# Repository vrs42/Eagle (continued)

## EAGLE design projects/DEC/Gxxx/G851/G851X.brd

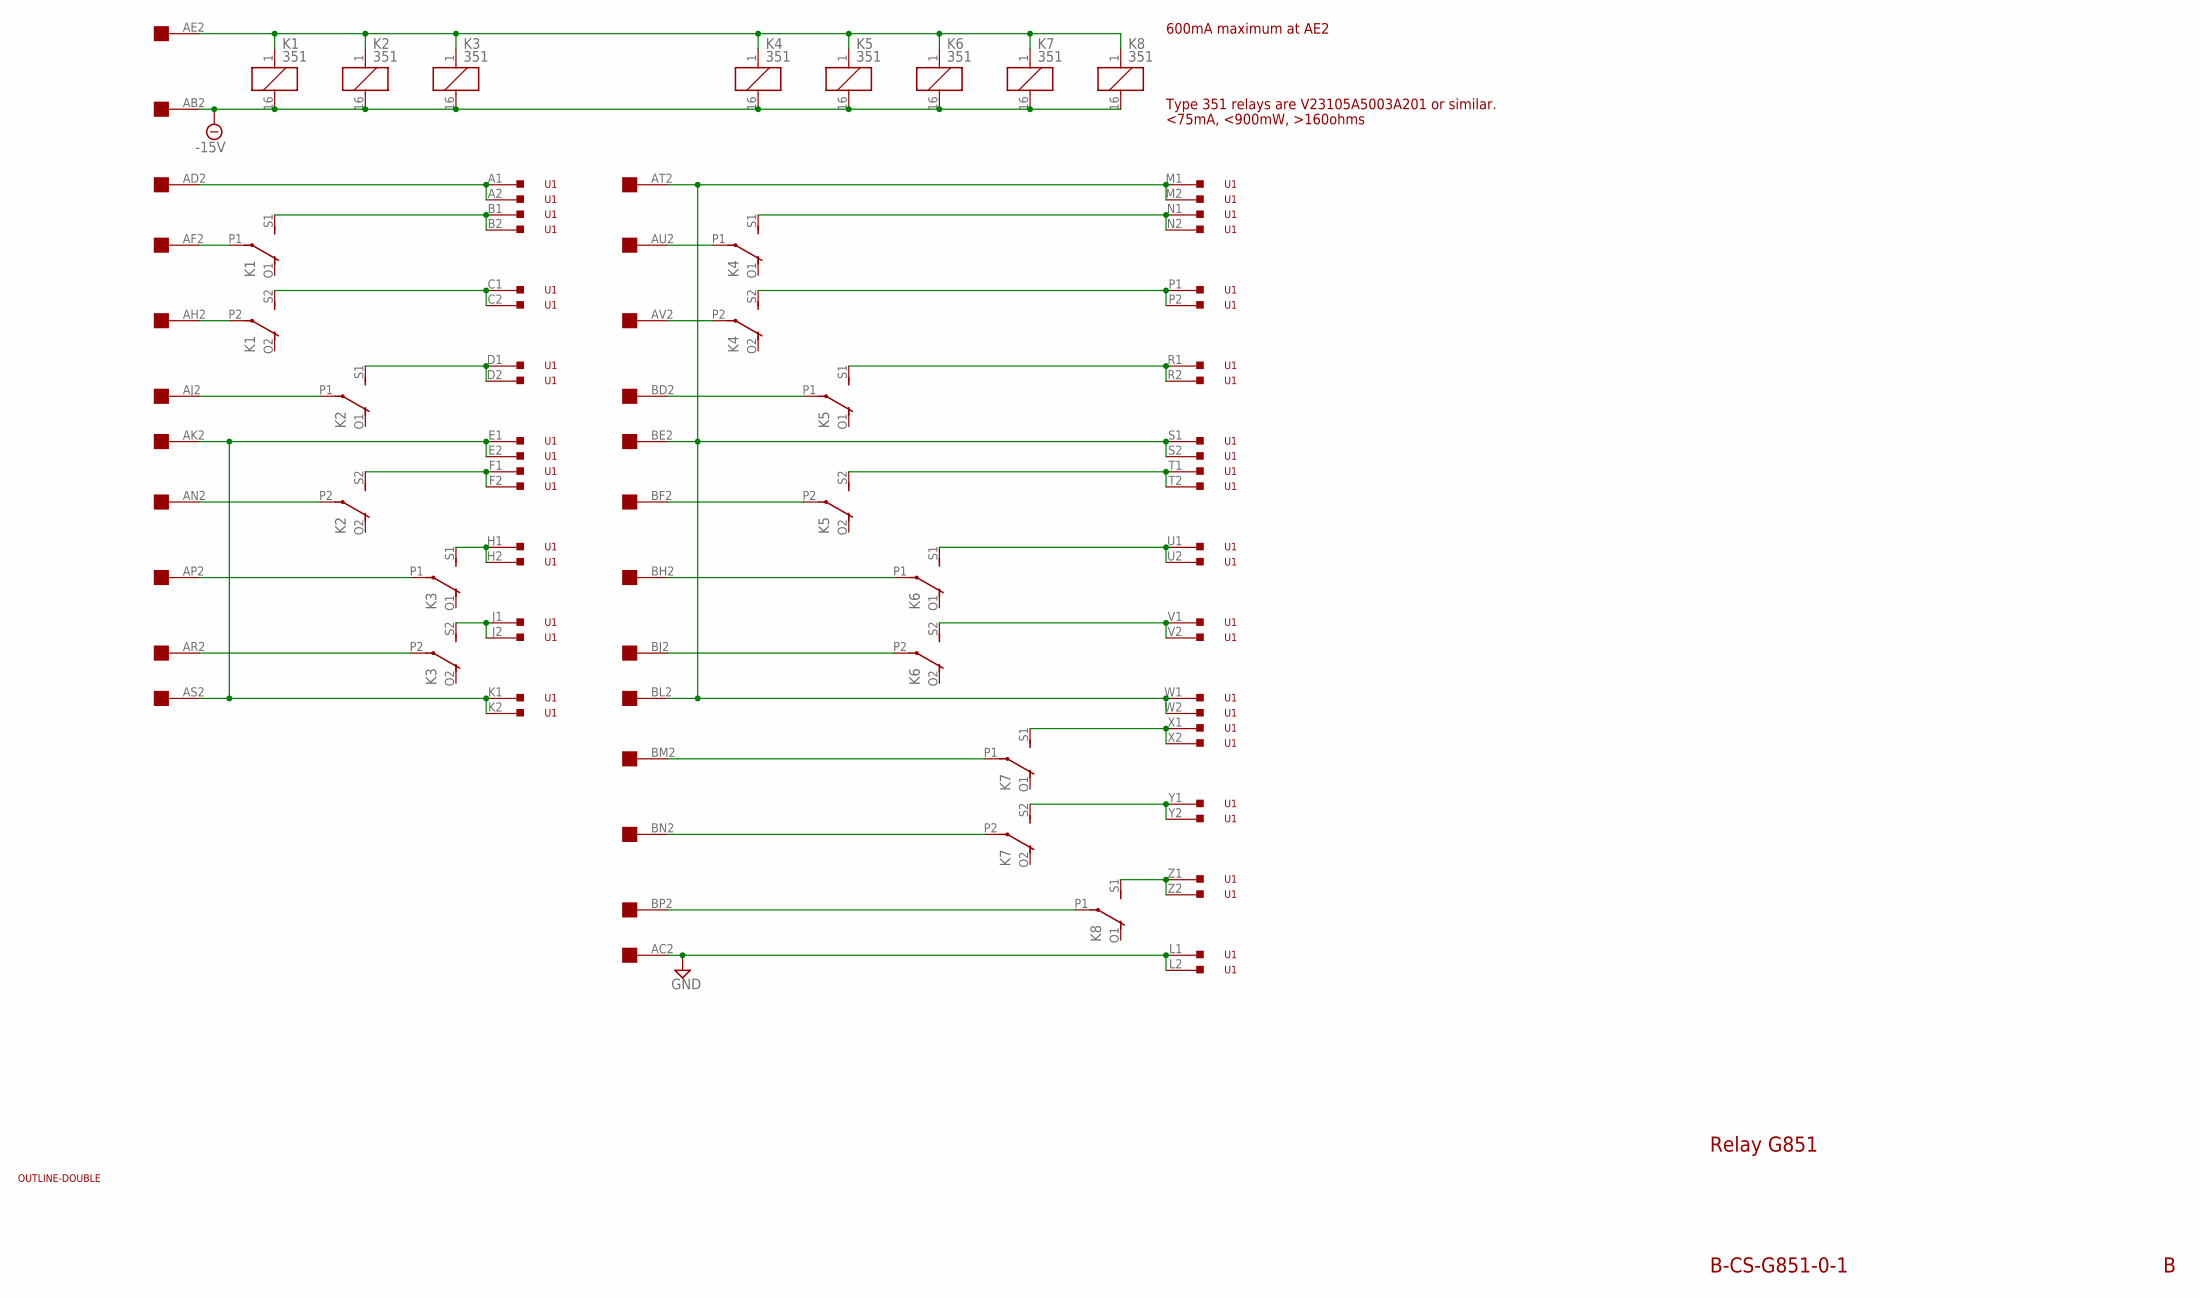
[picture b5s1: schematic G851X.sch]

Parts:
K1, K2, K3, K4, K5, K6, K7, K8: 351
U1: S7346-ND; 133-022-03
U$1: DOUBLE; EDGE-CON4
U$3: OUTLINE-DOUBLE; DOUBLE

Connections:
-15V: K1.16 (2), K2.16 (2), K3.16 (2), K4.16 (2), K5.16 (2), K6.16 (2), K7.16 (2), K8.16 (2), U$1.AB2
GND: U1.L1, U1.L2, U$1.AC2
unnamed: U1.A1, U1.A2, U$1.AD2
unnamed: K1.P1, U$1.AF2
unnamed: K1.P2, U$1.AH2
unnamed: K2.P1, U$1.AJ2
unnamed: K2.P2, U$1.AN2
unnamed: K3.P1, U$1.AP2
unnamed: K3.P2, U$1.AR2
unnamed: U1.E1, U1.E2, U1.K1, U1.K2, U$1.AK2, U$1.AS2
unnamed: U1.M1, U1.M2, U1.S1, U1.S2, U1.W1, U1.W2, U$1.AT2, U$1.BE2, U$1.BL2
unnamed: K7.P1, U$1.BM2
unnamed: K7.P2, U$1.BN2
unnamed: K8.P1, U$1.BP2
unnamed: K6.P2, U$1.BJ2
unnamed: K6.P1, U$1.BH2
unnamed: K5.P2, U$1.BF2
unnamed: K5.P1, U$1.BD2
unnamed: K4.P2, U$1.AV2
unnamed: K4.P1, U$1.AU2
unnamed: K1.1, K2.1, K3.1, K4.1, K5.1, K6.1, K7.1, K8.1, U$1.AE2
unnamed: K2.S1 (S), U1.D1, U1.D2
unnamed: K1.S2 (S), U1.C1, U1.C2
unnamed: K1.S1 (S), U1.B1, U1.B2
unnamed: K7.S2 (S), U1.Y1, U1.Y2
unnamed: K2.S2 (S), U1.F1, U1.F2
unnamed: K3.S1 (S), U1.H1, U1.H2
unnamed: K3.S2 (S), U1.J1, U1.J2
unnamed: K4.S1 (S), U1.N1, U1.N2
unnamed: K4.S2 (S), U1.P1, U1.P2
unnamed: K5.S1 (S), U1.R1, U1.R2
unnamed: K5.S2 (S), U1.T1, U1.T2
unnamed: K6.S1 (S), U1.U1, U1.U2
unnamed: K6.S2 (S), U1.V1, U1.V2
unnamed: K7.S1 (S), U1.X1, U1.X2
unnamed: K8.S1 (S), U1.Z1, U1.Z2

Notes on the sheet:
Relay G851
B-CS-G851-0-1
600mA maximum at AE2
Type 351 relays are V23105A5003A201 or similar.
<75mA, <900mW, >160ohms

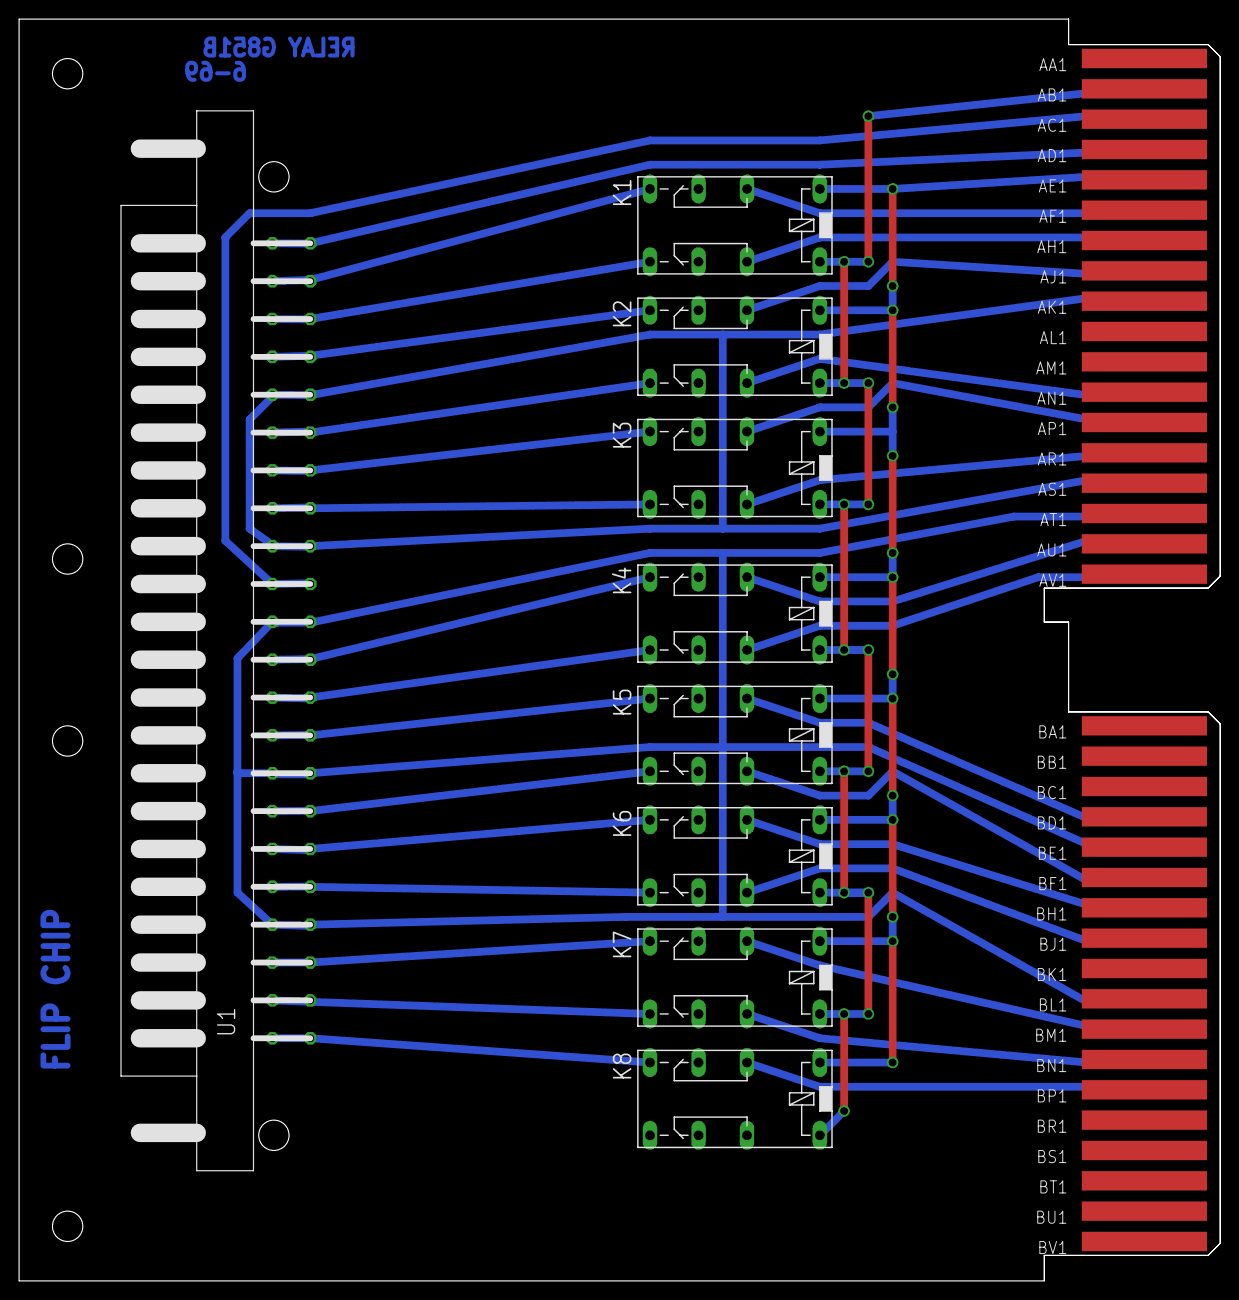
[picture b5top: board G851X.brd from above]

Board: 2 copper layers, 125.7 x 132.1 mm, 11 parts (0 on the bottom side), 36 nets.

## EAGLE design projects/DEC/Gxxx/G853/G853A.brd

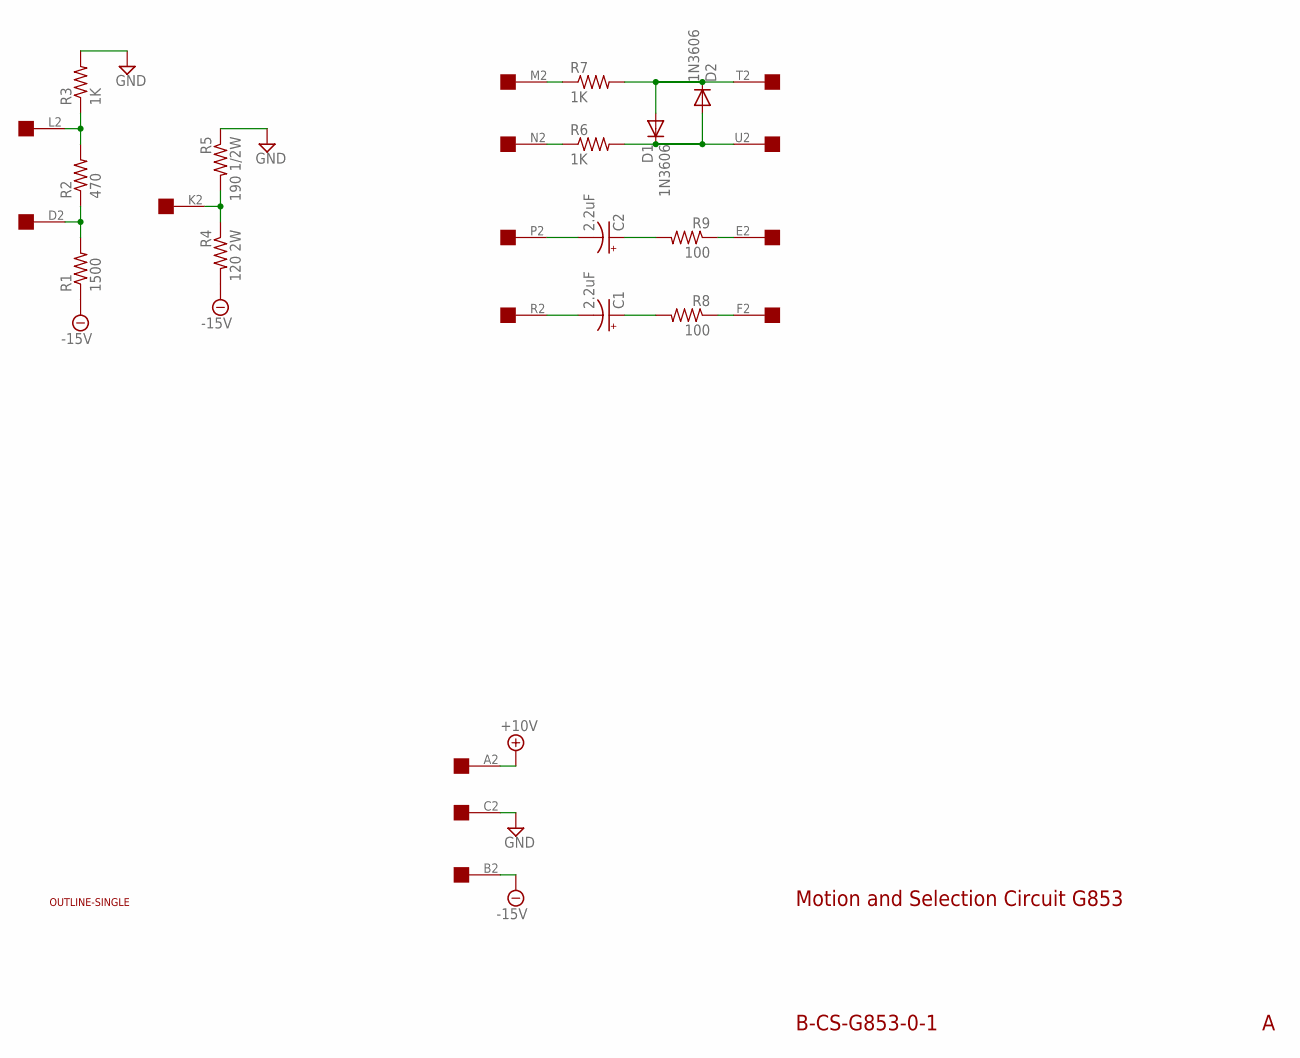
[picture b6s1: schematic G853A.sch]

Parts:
C1, C2: 2.2uF; E15-5
D1, D2: 1N3606; DO35-10
R1: 1500; 0207/10
R2: 470; 0207/10
R3, R6, R7: 1K; 0207/10
R4: 120 2W; P0817/22
R5: 190 1/2W; 0309/12
R8, R9: 100; 0207/10
U$1: OUTLINE-SINGLE; SINGLE
U$2: EDGE-1; EDGE-CON1

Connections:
+10V: U$2.A2
-15V: R1.1, R4.2, U$2.B2
GND: R3.2, R5.1, U$2.C2
unnamed: C1.-, U$2.R2
unnamed: C1.+, R8.2
unnamed: R1.2, R2.1, U$2.D2
unnamed: R6.1, U$2.N2
unnamed: R7.1, U$2.M2
unnamed: D1.A, D2.C, R7.2, U$2.T2
unnamed: D1.C, D2.A, R6.2, U$2.U2
unnamed: R2.2, R3.1, U$2.L2
unnamed: C2.+, R9.2
unnamed: C2.-, U$2.P2
unnamed: R8.1, U$2.F2
unnamed: R9.1, U$2.E2
unnamed: R4.1, R5.2, U$2.K2

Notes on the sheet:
Motion and Selection Circuit G853
B-CS-G853-0-1

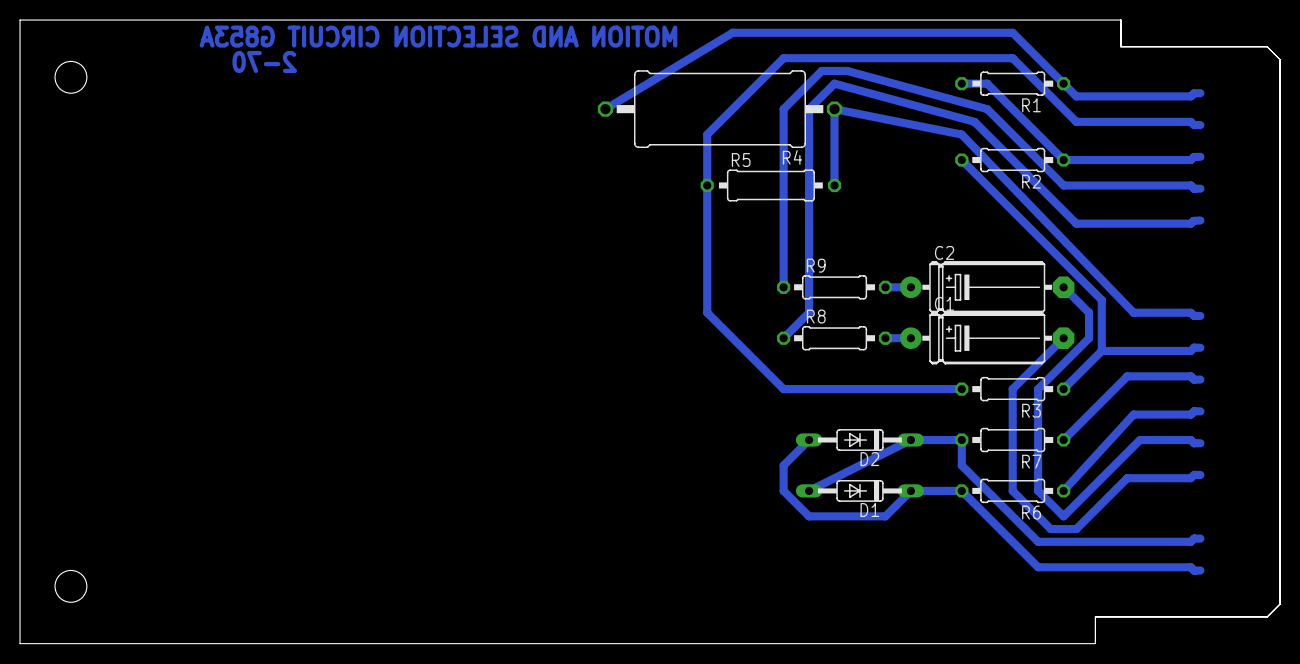
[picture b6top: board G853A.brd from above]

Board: 2 copper layers, 125.7 x 62.2 mm, 15 parts (0 on the bottom side), 15 nets.
